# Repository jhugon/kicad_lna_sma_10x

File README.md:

# Low Noise Amplifier SMA 10x Board in KiCAD

This KiCad board is a low noise amplifier with SMA input and output.

- 100 kHz to 20 MHz
- 10 times amplitude amplification
- ≤ 100 µV RMS noise
- AC coupled input

## Notes on Performance as-built

I've been setting +/- 5 V supplies, 20 mA current limit, with +/- 6V OVP and 25 mA OCP.

- Idle current: 9 mA with +/- 5 V supplies
- Current draw rises above 20 mA for large signals
- Noise 1478 µV RMS at output (without subtracting noise floor), with a broad bump around 8-10 MHz in the FFT
- In trying to analyze with a square wave, the AC-coupling low-pass filter frequency seems
  quite high compared to the bandwidth. Maybe it should be at 10 kHz instead of
  100 kHz?
- Sin response:
    - Gain peaks ~ 9 MHz at 17 dB
    - Gain -3 dB from peak a little above 10 MHz
- Step response:
    - 10-90% rise time: 22 ns
    - 0-99% rise time: 32 ns
    - Overshoot: 28%
    - 1 pct settling time: ~200 ns
- Hooked up to SiPM and LED pulser:
    - Detect pulses with 10s of mV peak heights
    - Ringing is evident, lasts ~ 250 ns
    - Pulse width 50-100 ns
    - Can't see pulse height quantization, it's just one big smeared gaussian

With 10 pF (leaded) decoupling cap soldered between U1 output and inverting input:

- Noise a bit lower than before; FFT is flat compared to a broad, low peak around 20 MHz before
- Sin response:
    - Gain max ~flat between 400 kHz and 100 MHz
    - Gain -3 dB from peak at 100 kHz and 3 MHz
- Step response:
    - Minimal overshoot/settling, probably overdamped now
    - 10-90% rise time: 112 ns
    - 0-99% rise time: 293 ns
    - Overshoot: <1%
    - 1 pct settling time: ~250 ns
- Hooked up to SiPM and LED pulser:
    - Pulse height seems lower than before
    - No ringing, maybe baseline is a bit lower on tail
    - Pulse width 100-150 ns
    - Can't see pulse height quantization, it's just one big smeared gaussian

## To-Do

- Decoupling cap(s) from V+ to V-?
- Compensation cap between gain-amp out and in-?
- Lower input blocking filter freq?
- Forgot about factor of 1/2 from 50 Ohm termination voltage divider--need extra factor of 2 gain
- Add input/output labels on SMAs
- Add +/- signs on DC in
- SMA terminator for noise measurements

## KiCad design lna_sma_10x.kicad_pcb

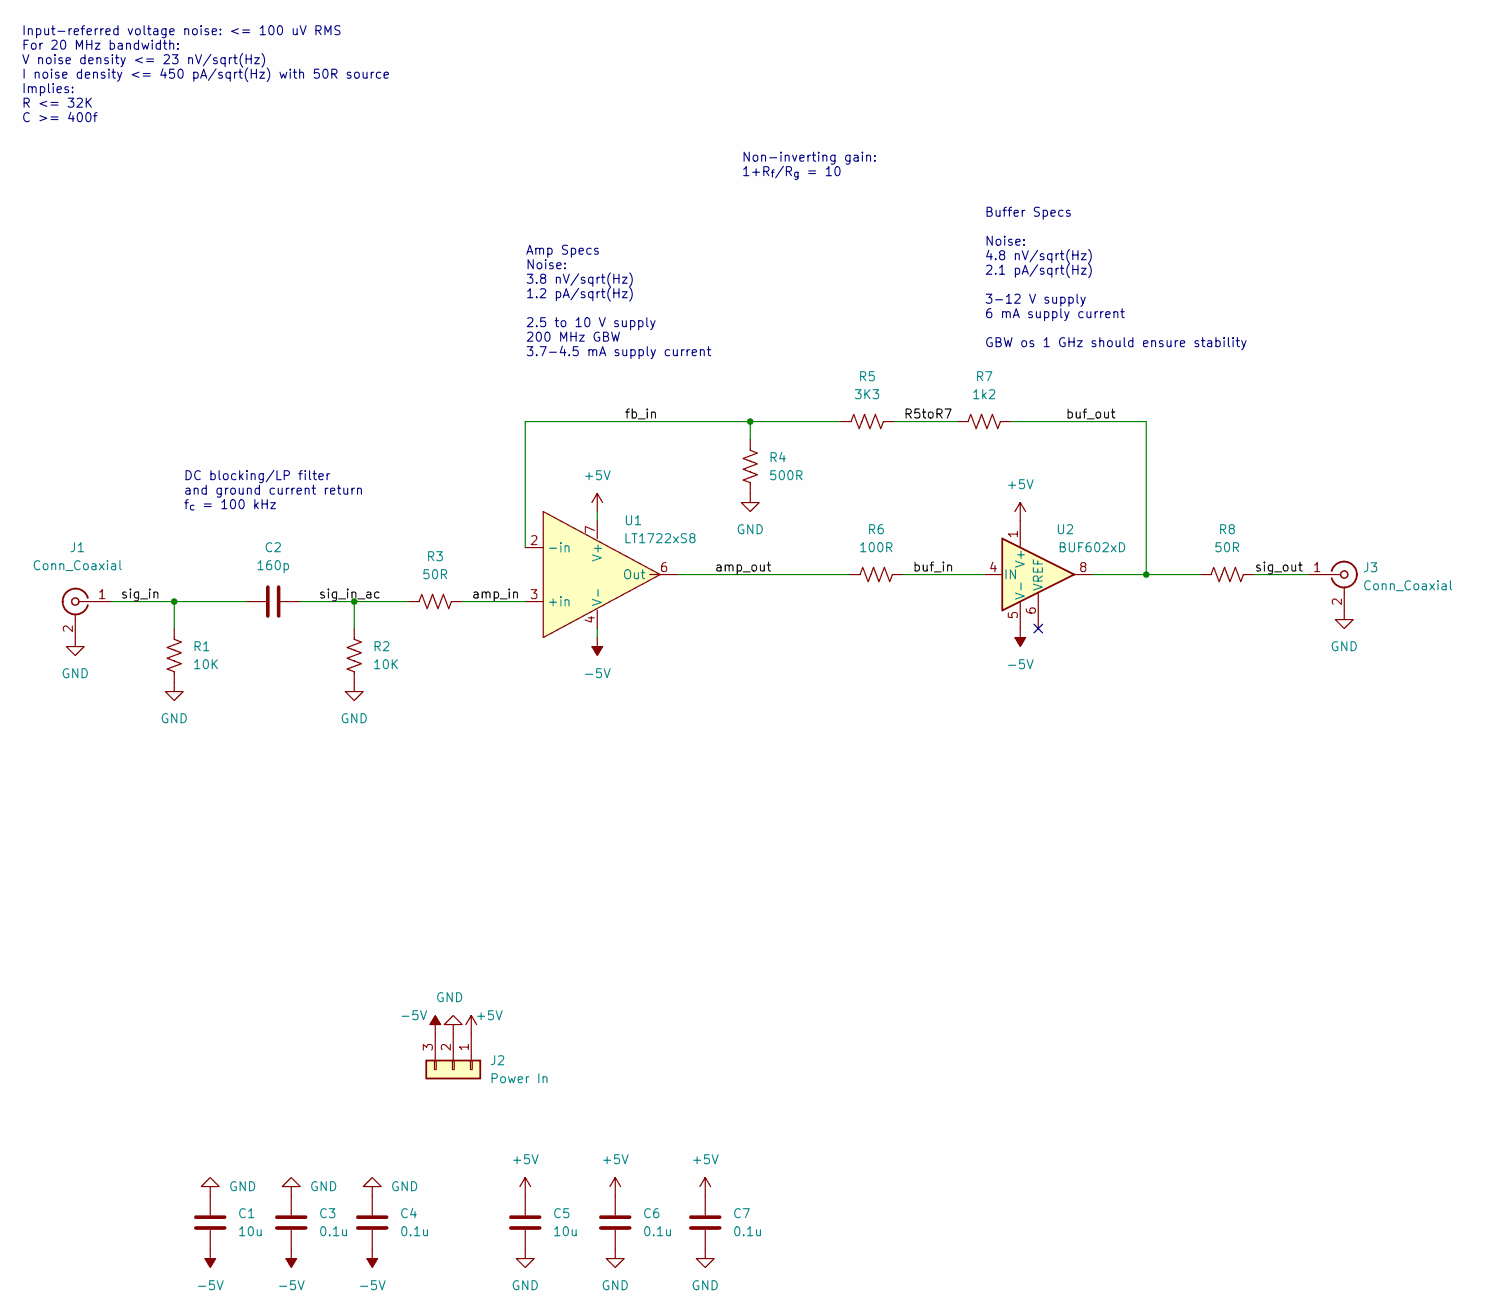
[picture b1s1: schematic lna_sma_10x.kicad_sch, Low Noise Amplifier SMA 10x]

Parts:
C1, C5: 10u; C_1206_3216Metric_Pad1.33x1.80mm_HandSolder; Mfr Part CL31A106KAHNNNF
C2: 160p; C_1206_3216Metric_Pad1.33x1.80mm_HandSolder; Mfr Part 12065A161JAT2A
C3, C4, C6, C7: 0.1u; C_1206_3216Metric_Pad1.33x1.80mm_HandSolder; Mfr Part CL31B104KBCNNND
J1, J3: Conn_Coaxial; SMA_Amphenol_132289_EdgeMount; Mfr Part 132289
J2: Power In; Molex_Nano-Fit_105313-xx03_1x03_P2.50mm_Horizontal; Mfr Part 105313-1303
R1, R2: 10K; R_1206_3216Metric_Pad1.30x1.75mm_HandSolder; Mfr Part CRCW120610K0FKEBC
R3, R8: 50R; R_1206_3216Metric_Pad1.30x1.75mm_HandSolder; Mfr Part CRCW120649R9FKEAC
R4: 500R; R_1206_3216Metric_Pad1.30x1.75mm_HandSolder; Mfr Part CRCW1206499RFKEAC
R5: 3K3; R_1206_3216Metric_Pad1.30x1.75mm_HandSolder; Mfr Part CRCW12063K32FKEAC
R6: 100R; R_1206_3216Metric_Pad1.30x1.75mm_HandSolder; Mfr Part CRCW1206100RFKEAC
R7: 1k2; R_1206_3216Metric_Pad1.30x1.75mm_HandSolder; Mfr Part CRCW12061K20FKEAC
U1: LT1722xS8; SOIC-8_3.9x4.9mm_P1.27mm; Mfr Part LT1722CS8#PBF
U2: BUF602xD; SOIC-8_3.9x4.9mm_P1.27mm; Mfr Part BUF602ID

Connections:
+5V: C5.2, C6.2, C7.2, J2.1, U1.7 (V+), U2.1 (V+)
-5V: C1.1, C3.1, C4.1, J2.3, U1.4 (V-), U2.5 (V-)
/R5toR7: R5.2, R7.1
/amp_in: R3.2, U1.3 (+in)
/amp_out: R6.1, U1.6 (Out)
/buf_in: R6.2, U2.4 (IN)
/buf_out: R7.2, R8.1, U2.8
/fb_in: R4.2, R5.1, U1.2 (-in)
/sig_in: C2.1, J1.1 (In), R1.1
/sig_in_ac: C2.2, R2.1, R3.1
/sig_out: J3.1 (In), R8.2
GND: C1.2, C3.2, C4.2, C5.1, C6.1, C7.1, J1.2 (Ext), J2.2, J3.2 (Ext), R1.2, R2.2, R4.1

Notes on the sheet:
Amp Specs Noise: 3.8 nV/sqrt(Hz) 1.2 pA/sqrt(Hz) 2.5 to 10 V supply 200 MHz GBW 3.7-4.5 mA supply current
DC blocking/LP filter and ground current return f_{c} = 100 kHz
Non-inverting gain: 1+R_{f}/R_{g} = 10
Buffer Specs Noise: 4.8 nV/sqrt(Hz) 2.1 pA/sqrt(Hz) 3-12 V supply 6 mA supply current GBW os 1 GHz should ensure stability
Input-referred voltage noise: <= 100 uV RMS For 20 MHz bandwidth: V noise density <= 23 nV/sqrt(Hz) I noise density <= 450 pA/sqrt(Hz) with 50R source Implies: R <= 32K C >= 400f

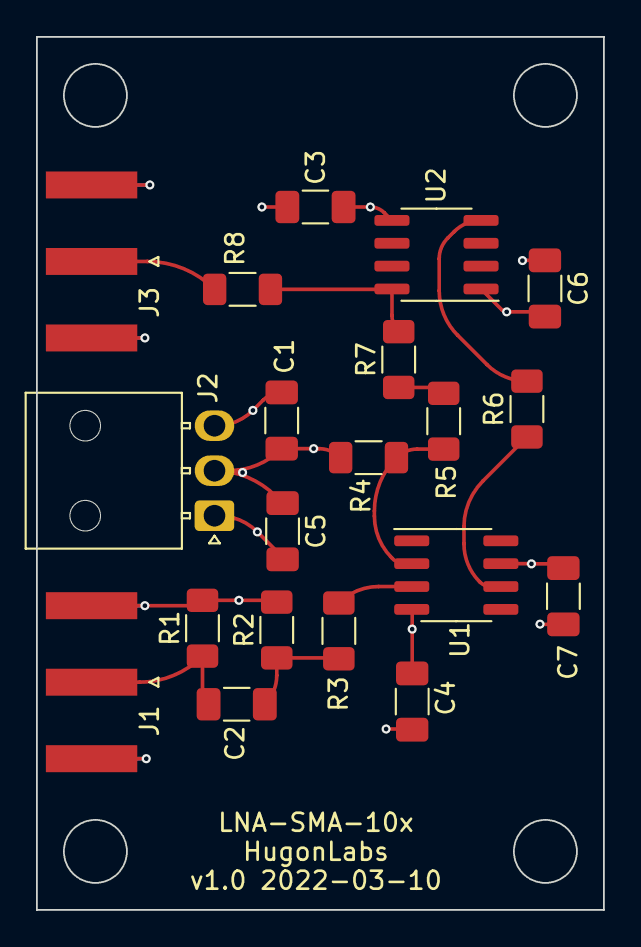
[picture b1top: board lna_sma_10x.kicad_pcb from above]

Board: 4 copper layers, 31.5 x 48.5 mm, 20 parts (0 on the bottom side), 12 nets.

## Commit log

2022-03-03 Initial schematic complete
    added New_Library with LT1722
    added schematic.pdf
2022-03-10 Schematic & BOM complete
    Split feedback R into 2 in series to get standard values
    Added power connector to library to have output power pins
    Added part numbers, data sheets, footprints in BOM
2022-03-10 PCB Placement, setup for 4 layers
2022-03-10 Defined PCB edges and holes
2022-03-10 PCB routed and planes filled
2022-03-10 completed silkscreen and bumped to 1.0
2022-03-10 Generated gerbers for v1.0--final
2022-04-07 Added README notes on performance
2022-04-11 added results to README
2022-04-22 added further test results to README.md
2022-04-28 now use git submodule kicad_hugonlib for libs
    moved power nano-fit over there and deleted New_Library
